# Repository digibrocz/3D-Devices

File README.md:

# Repository for DIGIBRO CZECH REPUBLIC
Application development, 
3D devices development, 
device FW development

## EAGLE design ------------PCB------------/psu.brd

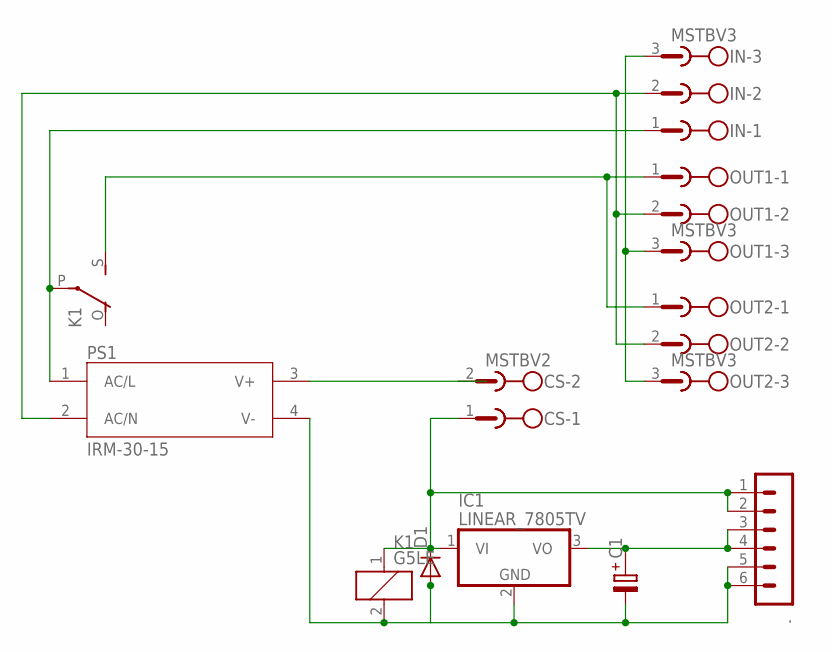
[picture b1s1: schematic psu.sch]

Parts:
.: MA06-1
C1: C-PR-2,0X5; E2,0-5
CS: MSTBV2
D1: DIODE-D-2.5; D-2.5
IC1: LINEAR_7805TV; LINEAR_TO220V
IN: MSTBV3
K1: G5LE
OUT1, OUT2: MSTBV3
PS1: IRM-30-15; CONV_IRM-30-15

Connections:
unnamed: IN.1, K1.P, PS1.1 (AC/L)
unnamed: ..1, ..2, CS.1, D1.C, IC1.1 (VI), K1.1
unnamed: K1.S, OUT1.1, OUT2.1
unnamed: IN.2, OUT1.2, OUT2.2, PS1.2 (AC/N)
unnamed: IN.3, OUT1.3, OUT2.3
unnamed: ..3, ..4, C1.+, IC1.3 (VO)
unnamed: CS.2, PS1.3 (V+)
unnamed: ..5, ..6, C1.-, D1.A, IC1.2 (GND), K1.2, PS1.4 (V-)

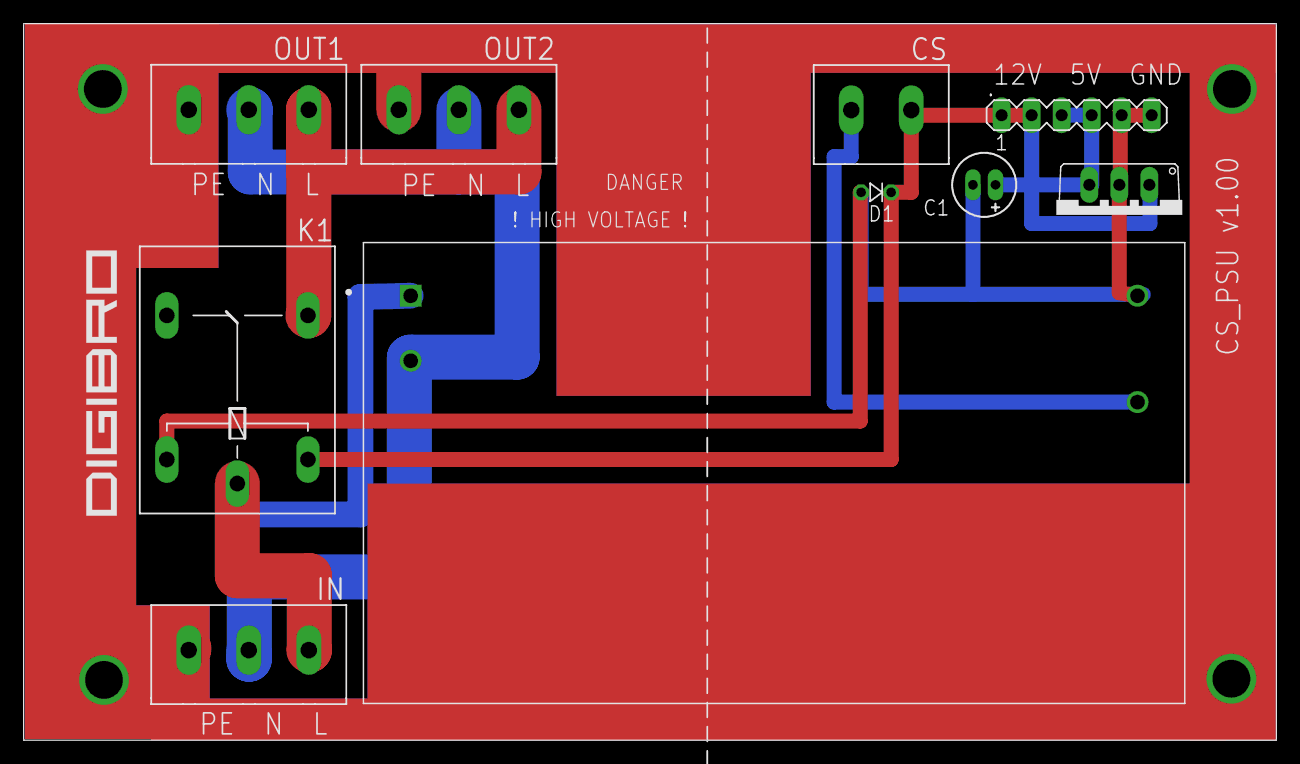
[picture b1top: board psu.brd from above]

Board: 2 copper layers, 106.0 x 60.6 mm, 10 parts (0 on the bottom side), 8 nets.

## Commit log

2021-04-08 First commit
    Basic DigibroCZ repo commit
2021-04-08 printer-update
2021-04-09 REPO_UPDATE
2021-04-09 DEBUG_UPLOAD
2021-04-13 dev-update
2021-04-15 upgrade
2021-04-20 PCB-PSU-UPLOAD
2021-04-22 Objednano 22.4.2021
2021-04-27 ProtoprintExt Beta

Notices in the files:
parts and their libraries:
cap-pan40: Copyright (C) 2004, Bob Starr
